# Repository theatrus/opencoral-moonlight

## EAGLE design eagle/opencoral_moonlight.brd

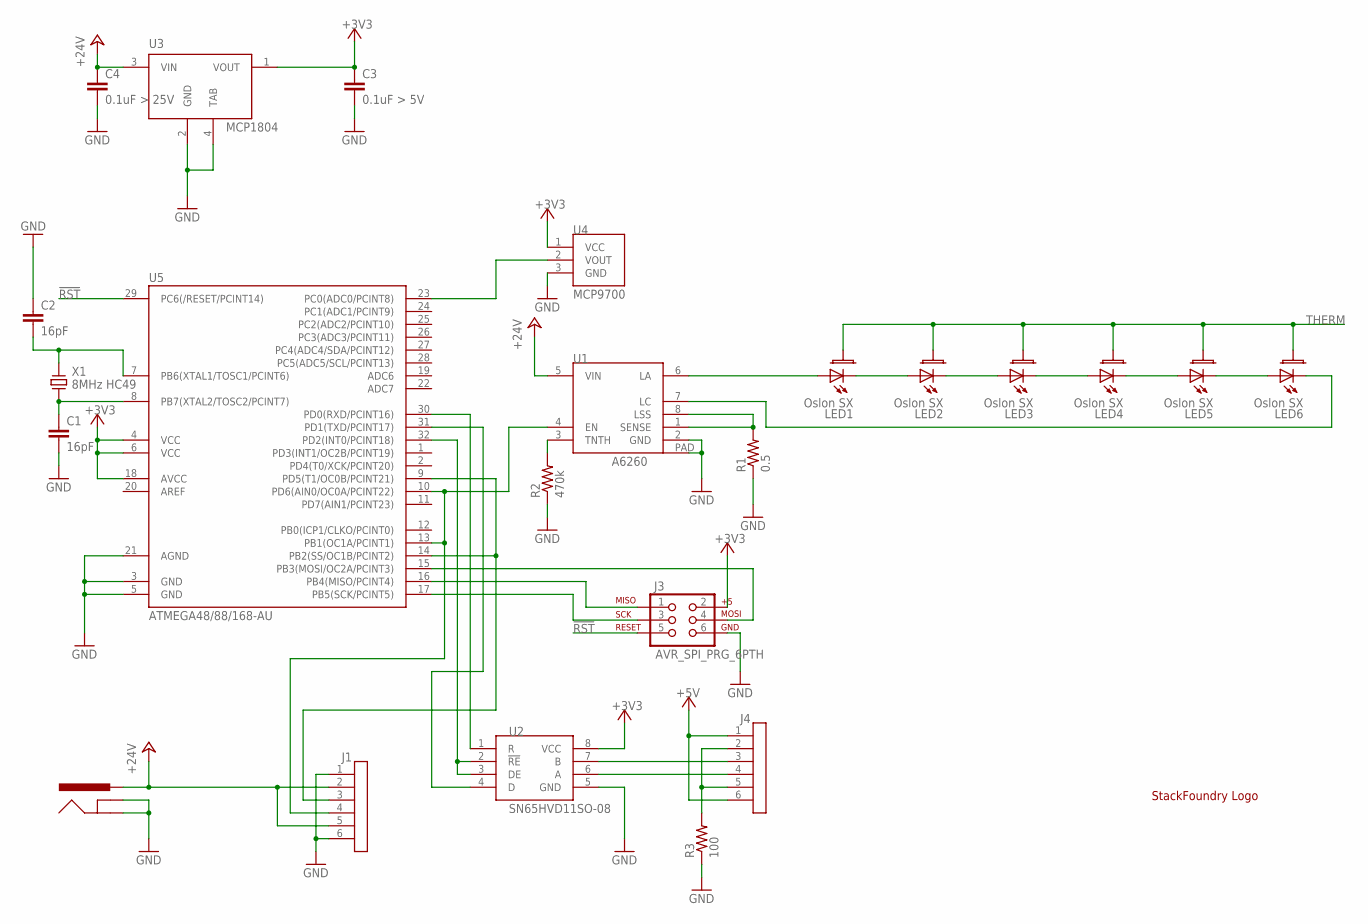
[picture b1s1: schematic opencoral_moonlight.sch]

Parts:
C1, C2: 16pF; C0603
C3: 0.1uF > 5V; C0603
C4: 0.1uF > 25V; C0603
J1, J4: RJ12; A-2004-RJ12
J2: POWER_JACKPTH; POWER_JACK_PTH
J3: AVR_SPI_PRG_6PTH; 2X3
LED1, LED2, LED3, LED4, LED5, LED6: Oslon SX; OSRAM_OSLON_SX
LOGO1: SFLOGO
R1: 0.5; R0805
R2: 470k; R0603
R3: 100; R0603
U1: A6260; ESOIC-8
U2: SN65HVD11SO-08; SO-08
U3: MCP1804; SOT223-3
U4: MCP9700; SOT23
U5: ATMEGA48/88/168-AU; TQFP32-08
X1: 8MHz HC49; HCM49

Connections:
!RST: J3.5, U5.29 (PC6(/RESET/PCINT14))
+3V3: C3.1, J3.2, U2.8 (VCC), U3.1 (VOUT), U4.1 (VCC), U5.4 (VCC), U5.6 (VCC), U5.18 (AVCC)
+5V: J4.1, J4.6
+24V: C4.1, J1.2, J1.5, J2.PWR, U1.5 (VIN), U3.3 (VIN)
GND: C1.2, C2.1, C3.2, C4.2, J1.1, J1.6, J2.GND, J2.GNDBREAK, J3.6, R1.1, R2.1, R3.1, U1.2 (GND), U1.PAD, U2.5 (GND), U3.2 (GND), U3.4 (TAB), U4.3 (GND), U5.3 (GND), U5.5 (GND), U5.21 (AGND)
unnamed: LED1.A, U1.6 (LA)
unnamed: LED1.C, LED2.A
unnamed: LED2.C, LED3.A
unnamed: LED3.C, LED4.A
unnamed: LED4.C, LED5.A
unnamed: LED5.C, LED6.A
unnamed: LED6.C, U1.7 (LC)
unnamed: J1.4, U1.4 (EN), U5.10 (PD6(AIN0/OC0A/PCINT22)), U5.13 (PB1(OC1A/PCINT1))
unnamed: U2.4 (D), U5.31 (PD1(TXD/PCINT17))
unnamed: U2.1 (R), U5.30 (PD0(RXD/PCINT16))
unnamed: R1.2, U1.1 (SENSE), U1.8 (LSS)
unnamed: U2.2 (!RE), U2.3 (DE), U5.32 (PD2(INT0/PCINT18))
unnamed: J4.3, U2.7 (B)
unnamed: J4.4, U2.6 (A)
unnamed: R2.2, U1.3 (TNTH)
unnamed: J1.3, U5.9 (PD5(T1/OC0B/PCINT21)), U5.14 (PB2(SS/OC1B/PCINT2))
unnamed: J3.4, U5.15 (PB3(MOSI/OC2A/PCINT3))
unnamed: J3.1, U5.16 (PB4(MISO/PCINT4))
unnamed: J3.3, U5.17 (PB5(SCK/PCINT5))
unnamed: C2.2, U5.7 (PB6(XTAL1/TOSC1/PCINT6)), X1.P$1
unnamed: C1.1, U5.8 (PB7(XTAL2/TOSC2/PCINT7)), X1.P$2
unnamed: U4.2 (VOUT), U5.23 (PC0(ADC0/PCINT8))
unnamed: J4.2, J4.5, R3.2
THERM: LED1.THERM, LED2.THERM, LED3.THERM, LED4.THERM, LED5.THERM, LED6.THERM

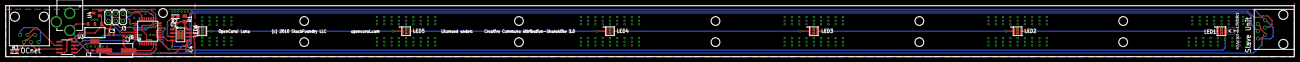
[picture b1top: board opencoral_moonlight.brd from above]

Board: 2 copper layers, 449.6 x 17.8 mm, 24 parts (0 on the bottom side), 29 nets.

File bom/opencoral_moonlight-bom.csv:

Partlist exported from /Users/atrus/Dropbox/elec/pr/opencoral_moonlight/rev0/opencoral_moonlight.sch at 9/19/11 11:29 PM

Part  Value              Device             Package        Description                         
C1    16pF               C-EUC0603          C0603          CAPACITOR, European symbol          
C2    16pF               C-EUC0603          C0603          CAPACITOR, European symbol          
C3    0.1uF > 5V         C-EUC0603          C0603          CAPACITOR, European symbol          
C4    0.1uF > 25V        C-EUC0603          C0603          CAPACITOR, European symbol          
J1    RJ12               RJ12               A-2004-RJ12                                        
J2    POWER_JACKPTH      POWER_JACKPTH      POWER_JACK_PTH Power Jack                          
J3    AVR_SPI_PRG_6PTH   AVR_SPI_PRG_6PTH   2X3            AVR ISP 6 Pin                       
J4    RJ12               RJ12               A-2004-RJ12                                        
LED1  Oslon SX           LEDOSLON_SX        OSRAM_OSLON_SX                                     
LED2  Oslon SX           LEDOSLON_SX        OSRAM_OSLON_SX                                     
LED3  Oslon SX           LEDOSLON_SX        OSRAM_OSLON_SX                                     
LED4  Oslon SX           LEDOSLON_SX        OSRAM_OSLON_SX                                     
LED5  Oslon SX           LEDOSLON_SX        OSRAM_OSLON_SX                                     
LED6  Oslon SX           LEDOSLON_SX        OSRAM_OSLON_SX                                     
LOGO1 SFLOGO             SFLOGO             SFLOGO                                             
R1    0.5                R-US_R0805         R0805          RESISTOR, American symbol           
R2    470k               R-US_R0603         R0603          RESISTOR, American symbol           
R3    100                R-US_R0603         R0603          RESISTOR, American symbol           
U1    A6260              A6260              ESOIC-8        Allegro A6260 Power LED Driver      
U2    SN65HVD11SO-08     SN65HVD11SO-08     SO-08          3.3V RS-485 Transceiver, Half-Duplex
U3    MCP1804            MCP1804            SOT223-3                                           
U4    MCP9700            MCP9700            SOT23          MCP9700 series temperature sensors  
U5    ATMEGA48/88/168-AU ATMEGA48/88/168-AU TQFP32-08                                          
X1    8MHz HC49          HCM49_18.432M      HCM49          18.432 MHz SMD Crystal

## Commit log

2014-04-08 OCLuna
2014-04-08 LICENSE and schem PDF

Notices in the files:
eagle/opencoral_moonlight.brd:
(c) 2010 StackFoundry LLC
Creative Commons Attribution-ShareAlike 3.0
Licensed under:
